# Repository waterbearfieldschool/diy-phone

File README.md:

# diy-phone

A from-scratch mobile phone: nRF52840 + SIM7600 cellular + e-ink display +
I2C keyboard. Texts, calls, contacts, a dial pad, and a serial console.

**Current version: [`v61e/`](v61e/) — see its [README](v61e/README.md).**

Each `vNN/` directory is a complete firmware snapshot; the version number
only ever goes up, so the highest one is the newest. Directories with an
`e` suffix (v45e onward) target the e-ink display; earlier versions drove
a 240x240 TFT.

The defining design idea of the current line: **all-driven partial
refreshes**. The SSD1681 only drives pixels that differ from its stored
"previous image" — and undriven pixels are what fade and ghost on this
panel. So the firmware writes each frame to the controller's current RAM
plane and the frame's *inverse* to the previous-image plane: every pixel
compares as changed, every pixel gets driven, and the panel delivers
crisp text on every quiet update — no fading, no ghosts, and no blinking
at all during use (full refreshes survive only at boot and as a rare
idle panel-care cycle). The full story, including the failed
approaches that mapped the panel's behavior, is in the v61e README.

Waypoints in the history: `v41` (the TFT firmware, restructured into
modules), `v44` (address book, missed calls, network timezone), `v45e`
(the e-ink port), `v53e` (voice calls), `v60e` (the all-driven refresh breakthrough), `v61e` (current).

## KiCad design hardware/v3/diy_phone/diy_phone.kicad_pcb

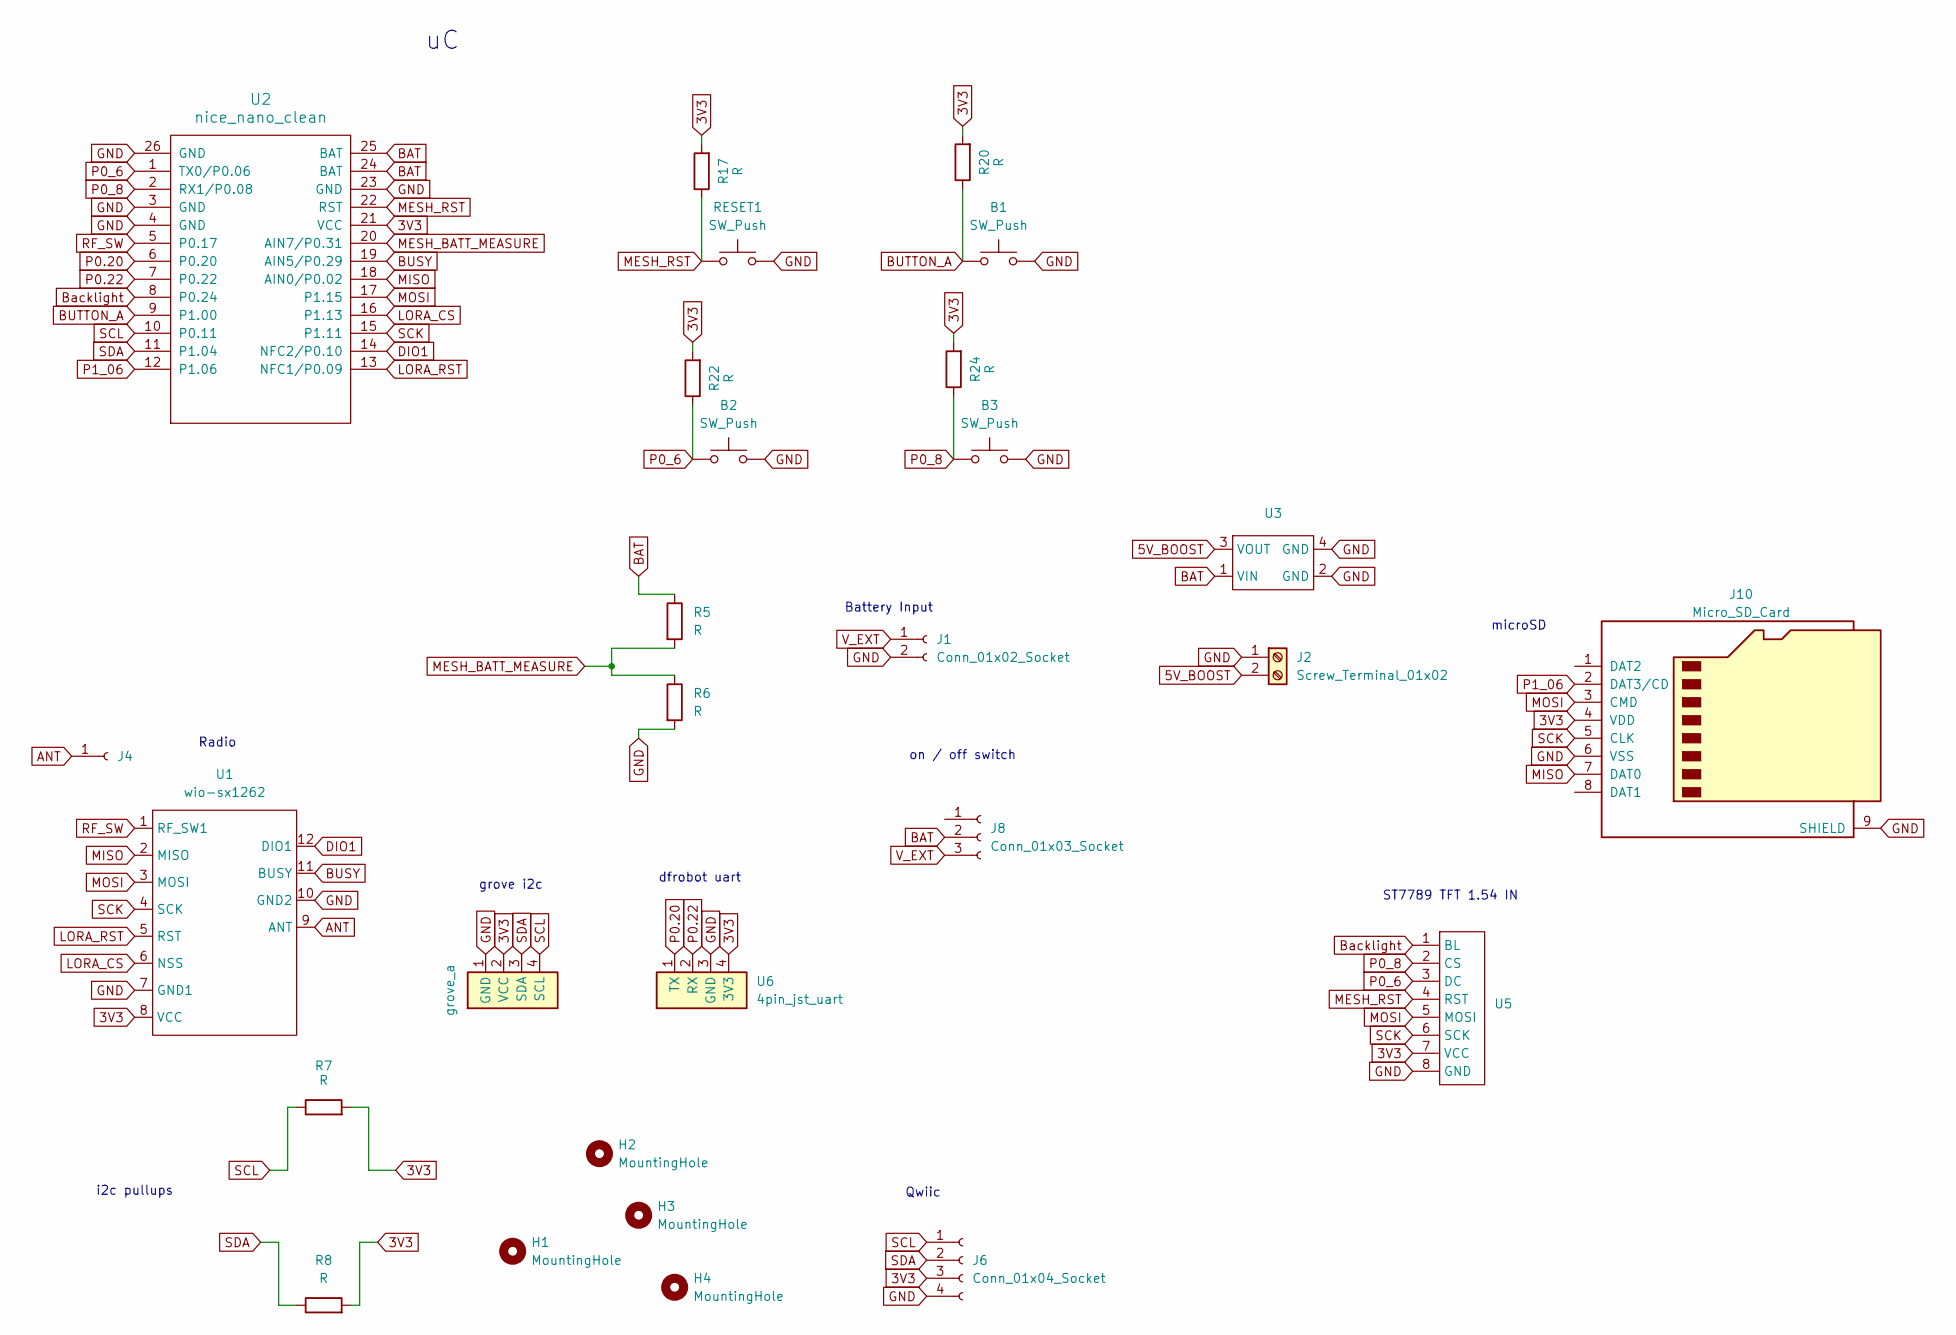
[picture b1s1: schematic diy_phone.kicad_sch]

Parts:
B1, B2, B3: SW_Push; SW_Tactile_SPST_Angled_PTS645Vx31-2LFS
H1, H2, H3, H4: MountingHole; MountingHole_3.2mm_M3
J1: Conn_01x02_Socket; JST_PH_B2B-PH-K_1x02_P2.00mm_Vertical
J2: Screw_Terminal_01x02; TerminalBlock_Phoenix_MKDS-1,5-2_1x02_P5.00mm_Horizontal
J4: Conn_01x01_Socket; PinSocket_1x01_P2.54mm_Vertical
J6: Conn_01x04_Socket; JST_SH4_SKINNY
J8: Conn_01x03_Socket; SSW_1825232-1
J10: Micro_SD_Card; DM3D-SF_outline
R5, R6, R7, R8, R17, R20, R22, R24: R; R_0805_2012Metric_Pad1.20x1.40mm_HandSolder
RESET1: SW_Push; SW_Tactile_SPST_Angled_PTS645Vx31-2LFS
U1: wio-sx1262; wio-sx1262-extended
U2: nice_nano_clean; nice_nano_cleanest
U3: tps61088_boost_amazon
U4: grove_a
U5: st7789_154in_240x240
U6: 4pin_jst_uart; grove_a

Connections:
3V3: J6.3, J10.4 (VDD), R7.2, R8.2, R17.2, R20.2, R22.2, R24.2, U1.8 (VCC), U2.21 (VCC), U4.2 (VCC), U5.7 (VCC), U6.4 (3V3)
5V_BOOST: J2.2, U3.3 (VOUT)
ANT: J4.1, U1.9 (ANT)
BAT: J8.2, R5.1, U2.24 (BAT), U2.25 (BAT), U3.1 (VIN)
BUSY: U1.11 (BUSY), U2.19 (AIN5/P0.29)
BUTTON_A: B1.1, R20.1, U2.9 (P1.00)
Backlight: U2.8 (P0.24), U5.1 (BL)
DIO1: U1.12 (DIO1), U2.14 (NFC2/P0.10)
GND: B1.2, B2.2, B3.2, J1.2, J2.1, J6.4, J10.6 (VSS), J10.9 (SHIELD), R6.2, RESET1.2, U1.7 (GND1), U1.10 (GND2), U2.3 (GND), U2.4 (GND), U2.23 (GND), U2.26 (GND), U3.2 (GND), U3.4 (GND), U4.1 (GND), U5.8 (GND), U6.3 (GND)
LORA_CS: U1.6 (NSS), U2.16 (P1.13)
LORA_RST: U1.5 (RST), U2.13 (NFC1/P0.09)
MESH_BATT_MEASURE: R5.2, R6.1, U2.20 (AIN7/P0.31)
MESH_RST: R17.1, RESET1.1, U2.22 (RST), U5.4 (RST)
MISO: J10.7 (DAT0), U1.2 (MISO), U2.18 (AIN0/P0.02)
MOSI: J10.3 (CMD), U1.3 (MOSI), U2.17 (P1.15), U5.5 (MOSI)
P0.20: U2.6 (P0.20), U6.1 (TX)
P0.22: U2.7 (P0.22), U6.2 (RX)
P0_6: B2.1, R22.1, U2.1 (TX0/P0.06), U5.3 (DC)
P0_8: B3.1, R24.1, U2.2 (RX1/P0.08), U5.2 (CS)
P1_06: J10.2 (DAT3/CD), U2.12 (P1.06)
RF_SW: U1.1 (RF_SW1), U2.5 (P0.17)
SCK: J10.5 (CLK), U1.4 (SCK), U2.15 (P1.11), U5.6 (SCK)
SCL: J6.1, R7.1, U2.10 (P0.11), U4.4 (SCL)
SDA: J6.2, R8.1, U2.11 (P1.04), U4.3 (SDA)
V_EXT: J1.1, J8.3

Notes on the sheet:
microSD
ST7789 TFT 1.54 IN
grove i2c
on / off switch
dfrobot uart
i2c pullups
Radio
Battery Input
Qwiic

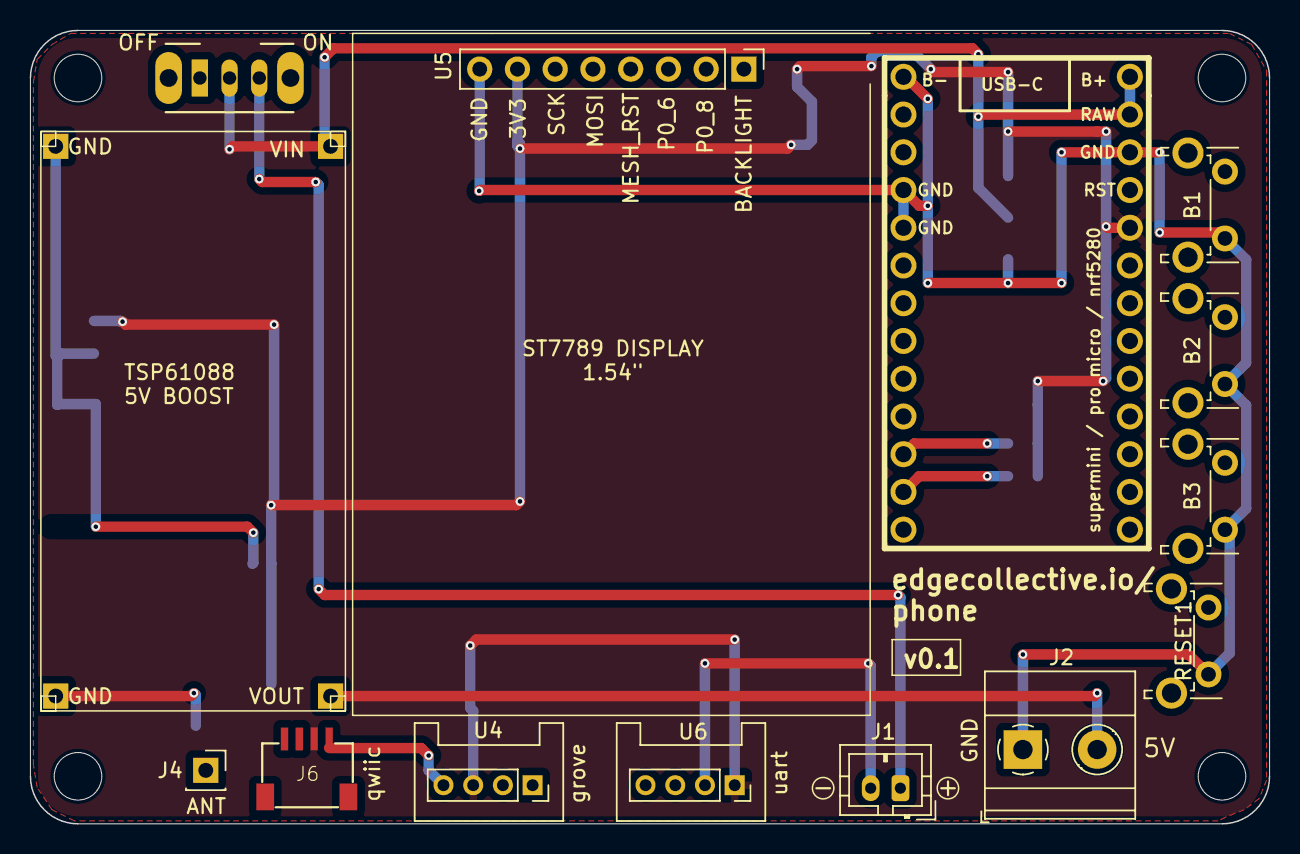
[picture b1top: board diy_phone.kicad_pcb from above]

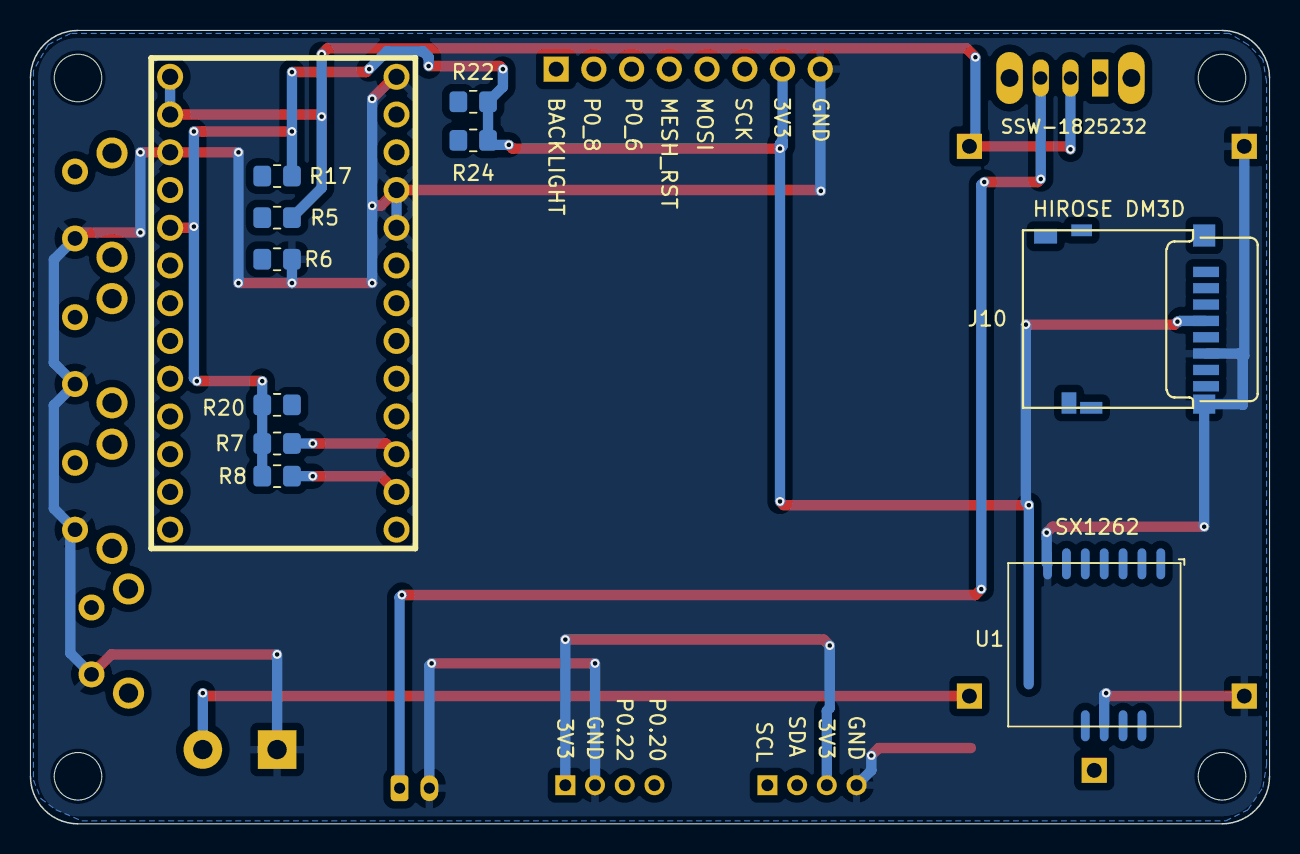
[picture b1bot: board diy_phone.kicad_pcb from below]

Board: 2 copper layers, 83.4 x 53.4 mm, 28 parts (10 on the bottom side), 25 nets.

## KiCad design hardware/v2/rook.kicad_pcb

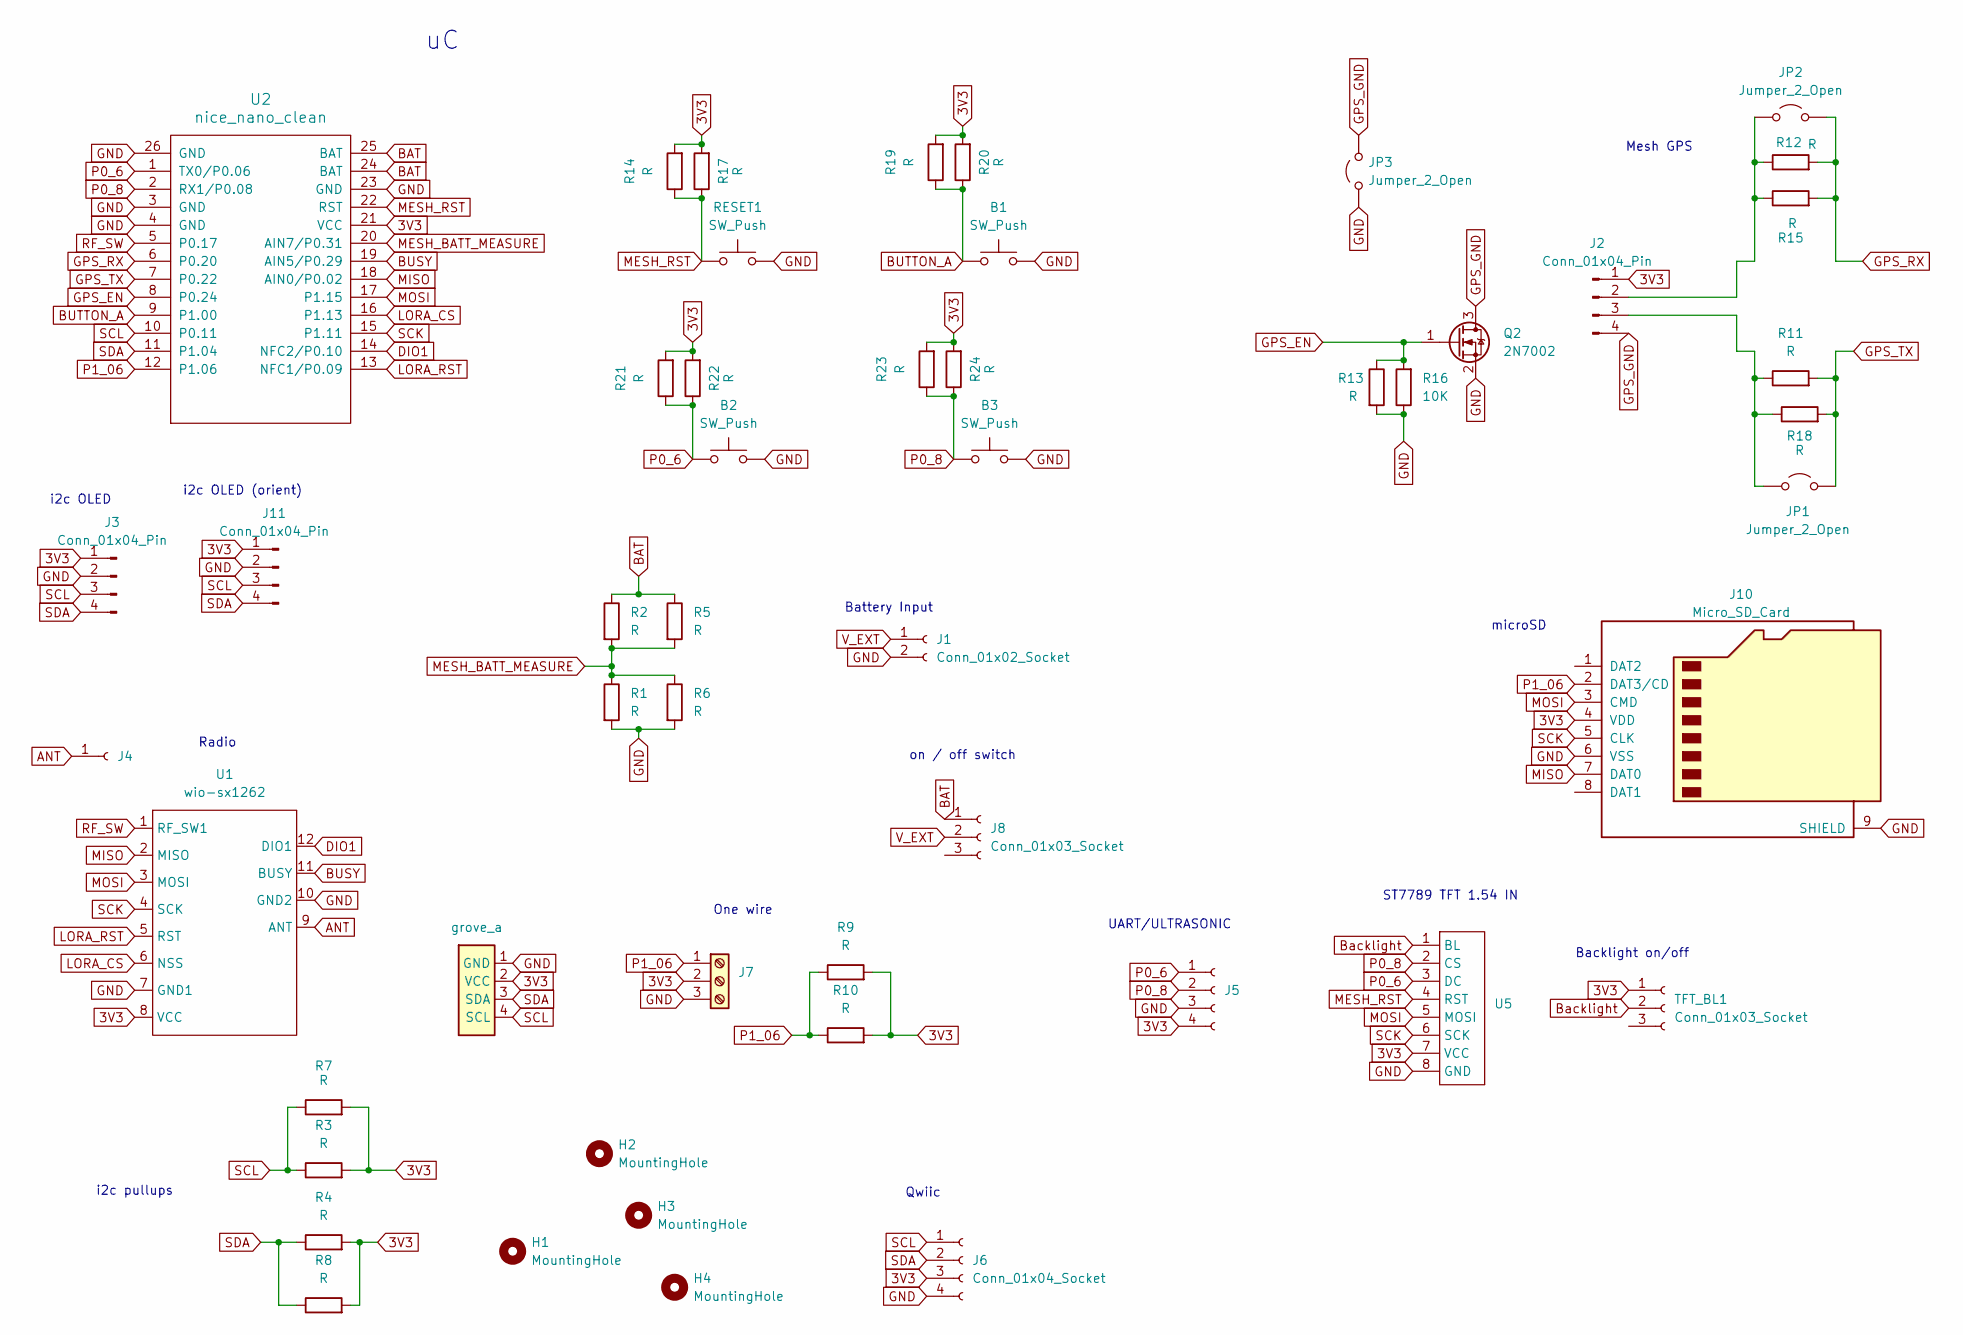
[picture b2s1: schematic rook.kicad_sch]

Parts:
B1, B2, B3: SW_Push; SW_Tactile_SPST_Angled_PTS645Vx31-2LFS
H1, H2, H3, H4: MountingHole; MountingHole_3.2mm_M3
J1: Conn_01x02_Socket; JST_PH_B2B-PH-K_1x02_P2.00mm_Vertical
J2: Conn_01x04_Pin; gps_ublox_blue
J3, J11: Conn_01x04_Pin; ssd1306_a
J4: Conn_01x01_Socket; PinSocket_1x01_P2.54mm_Vertical
J5: Conn_01x04_Socket; PinSocket_1x04_P2.54mm_Vertical
J6: Conn_01x04_Socket; JST_SH4_SKINNY
J7: Screw_Terminal_01x03; TerminalBlock_Phoenix_MKDS-1,5-3-5.08_1x03_P5.08mm_Horizont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
J8: Conn_01x03_Socket; SSW_1825232-1
J10: Micro_SD_Card; DM3D-SF_outline
JP1, JP2, JP3: Jumper_2_Open; SolderJumper-2_P1.3mm_Open_Pad1.0x1.5mm
Q2: 2N7002; SOT-23
R1, R2, R3, R4, R10, R11, R12, R13, R14, R19, R21, R23: R; R_Axial_DIN0207_L6.3mm_D2.5mm_P10.16mm_Horizontal
R5, R6, R7, R8, R9, R15, R17, R18, R20, R22, R24: R; R_0805_2012Metric_Pad1.20x1.40mm_HandSolder
R16: 10K; R_0805_2012Metric_Pad1.20x1.40mm_HandSolder
RESET1: SW_Push; SW_Tactile_SPST_Angled_PTS645Vx31-2LFS
TFT_BL1: Conn_01x03_Socket; SSW_1825232-1
U1: wio-sx1262; wio-sx1262-extended
U2: nice_nano_clean; nice_nano_cleanest
U4: grove_a
U5: st7789_154in_240x240

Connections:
3V3: J2.1, J3.1, J5.4, J6.3, J7.2, J10.4 (VDD), J11.1, R3.2, R4.2, R7.2, R8.2, R9.2, R10.2, R14.2, R17.2, R19.2, R20.2, R21.2, R22.2, R23.2, R24.2, TFT_BL1.1, U1.8 (VCC), U2.21 (VCC), U4.2 (VCC), U5.7 (VCC)
ANT: J4.1, U1.9 (ANT)
BAT: J8.1, R2.1, R5.1, U2.24 (BAT), U2.25 (BAT)
BUSY: U1.11 (BUSY), U2.19 (AIN5/P0.29)
BUTTON_A: B1.1, R19.1, R20.1, U2.9 (P1.00)
Backlight: TFT_BL1.2, U5.1 (BL)
DIO1: U1.12 (DIO1), U2.14 (NFC2/P0.10)
GND: B1.2, B2.2, B3.2, J1.2, J3.2, J5.3, J6.4, J7.3, J10.6 (VSS), J10.9 (SHIELD), J11.2, JP3.1 (A), Q2.2 (S), R1.2, R6.2, R13.2, R16.1, RESET1.2, U1.7 (GND1), U1.10 (GND2), U2.3 (GND), U2.4 (GND), U2.23 (GND), U2.26 (GND), U4.1 (GND), U5.8 (GND)
GPS_EN: Q2.1 (G), R13.1, R16.2, U2.8 (P0.24)
GPS_GND: J2.4, JP3.2 (B), Q2.3 (D)
GPS_RX: JP2.2 (B), R12.2, R15.2, U2.6 (P0.20)
GPS_TX: JP1.2 (B), R11.2, R18.2, U2.7 (P0.22)
LORA_CS: U1.6 (NSS), U2.16 (P1.13)
LORA_RST: U1.5 (RST), U2.13 (NFC1/P0.09)
MESH_BATT_MEASURE: R1.1, R2.2, R5.2, R6.1, U2.20 (AIN7/P0.31)
MESH_RST: R14.1, R17.1, RESET1.1, U2.22 (RST), U5.4 (RST)
MISO: J10.7 (DAT0), U1.2 (MISO), U2.18 (AIN0/P0.02)
MOSI: J10.3 (CMD), U1.3 (MOSI), U2.17 (P1.15), U5.5 (MOSI)
unnamed: J2.2, JP2.1 (A), R12.1, R15.1
unnamed: J2.3, JP1.1 (A), R11.1, R18.1
P0_6: B2.1, J5.1, R21.1, R22.1, U2.1 (TX0/P0.06), U5.3 (DC)
P0_8: B3.1, J5.2, R23.1, R24.1, U2.2 (RX1/P0.08), U5.2 (CS)
P1_06: J7.1, J10.2 (DAT3/CD), R9.1, R10.1, U2.12 (P1.06)
RF_SW: U1.1 (RF_SW1), U2.5 (P0.17)
SCK: J10.5 (CLK), U1.4 (SCK), U2.15 (P1.11), U5.6 (SCK)
SCL: J3.3, J6.1, J11.3, R3.1, R7.1, U2.10 (P0.11), U4.4 (SCL)
SDA: J3.4, J6.2, J11.4, R4.1, R8.1, U2.11 (P1.04), U4.3 (SDA)
V_EXT: J1.1, J8.2

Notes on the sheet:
microSD
Mesh GPS
ST7789 TFT 1.54 IN
Backlight on/off
on / off switch
One wire
i2c pullups
i2c OLED
Radio
UART/ULTRASONIC
i2c OLED (orient)
Battery Input
Qwiic

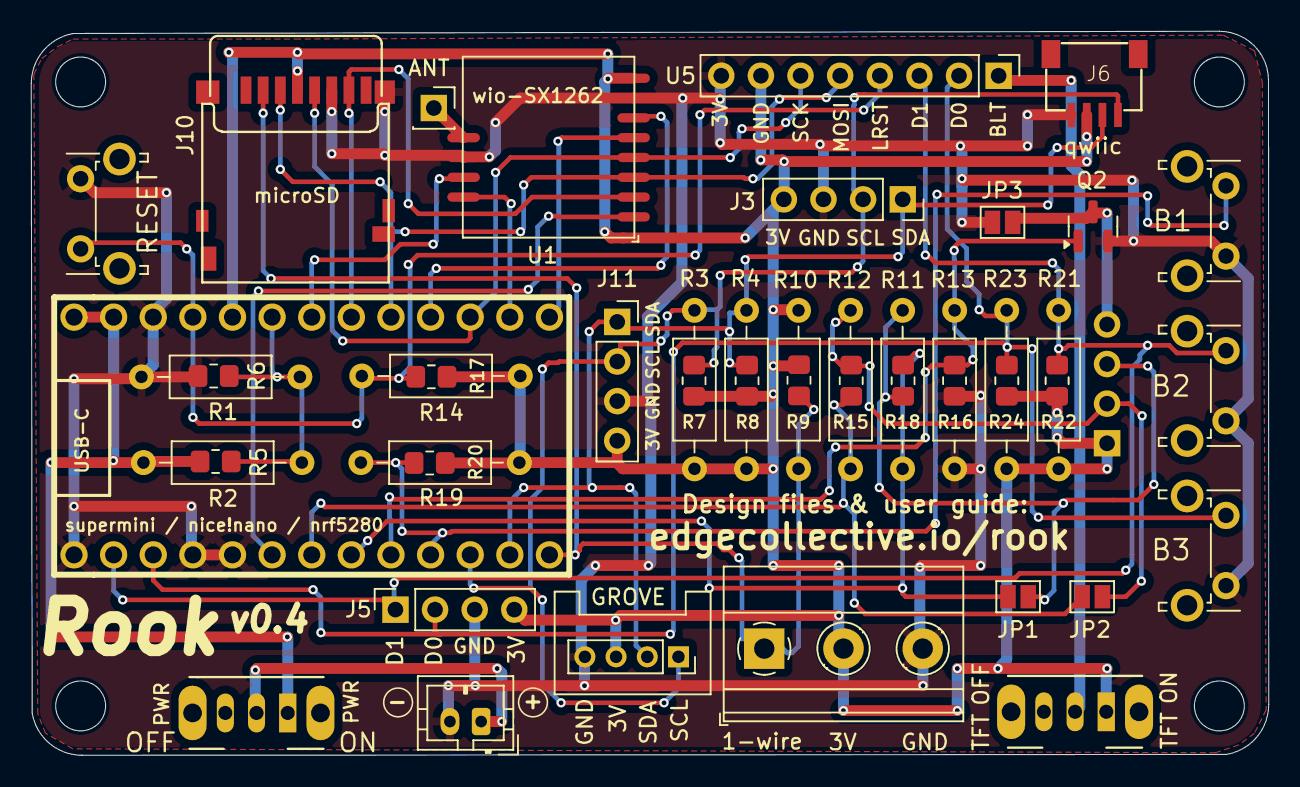
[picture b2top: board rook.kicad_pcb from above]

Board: 2 copper layers, 79.3 x 46.4 mm, 51 parts (1 on the bottom side), 28 nets.

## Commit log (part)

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2025-12-26 v7/p26.py is pretty good
2026-01-08 version v32 works fairly well
